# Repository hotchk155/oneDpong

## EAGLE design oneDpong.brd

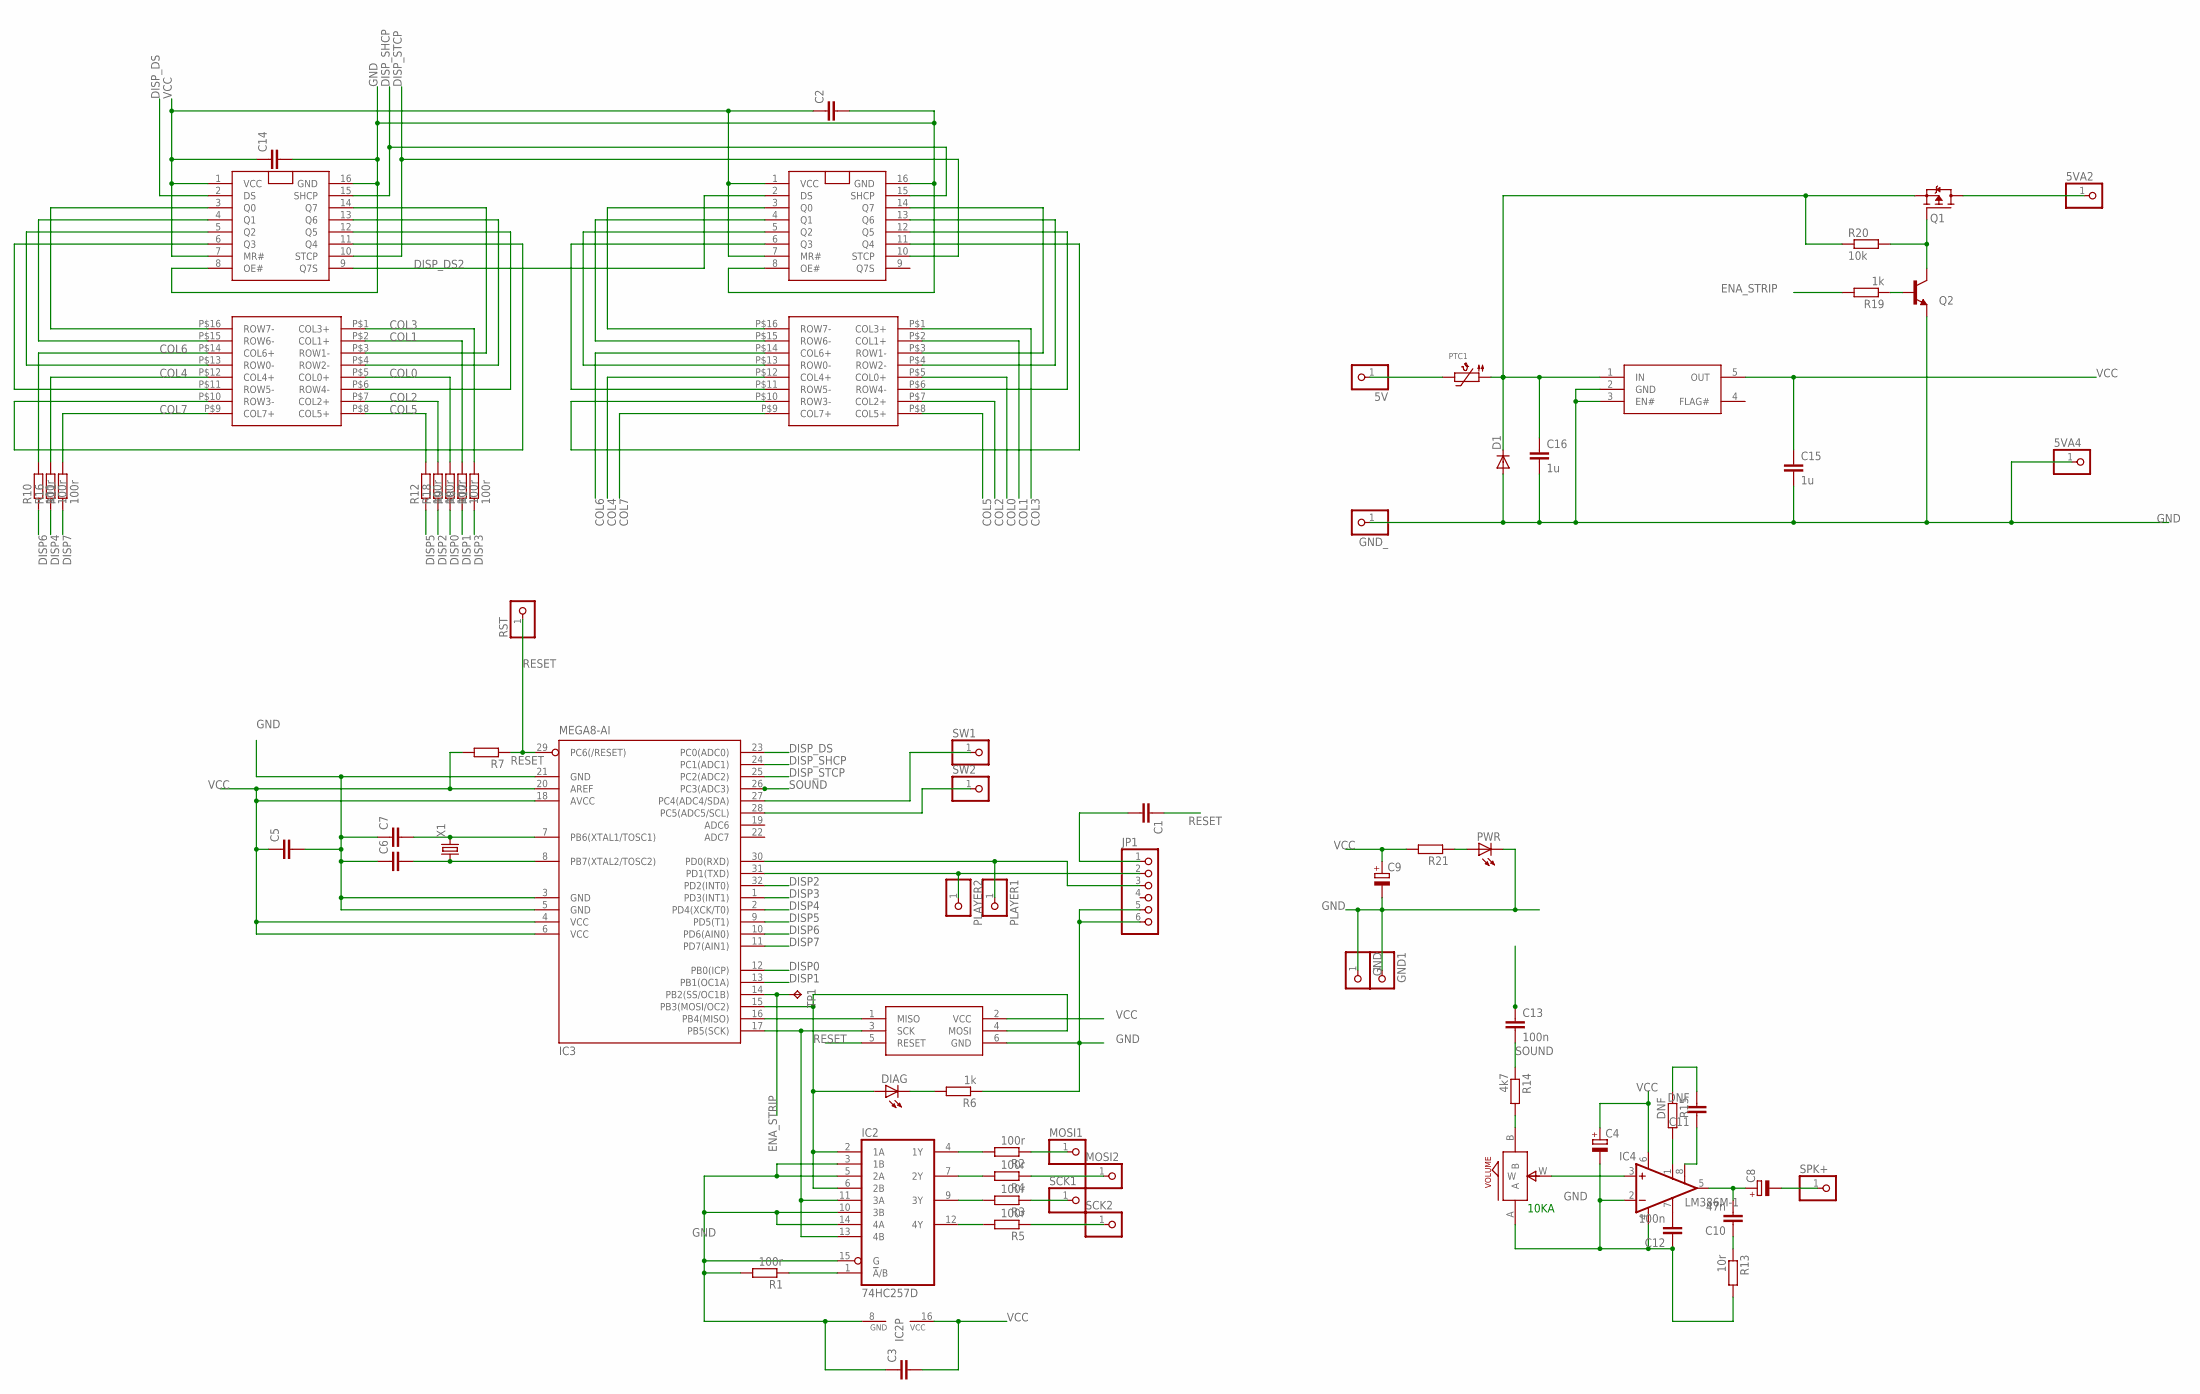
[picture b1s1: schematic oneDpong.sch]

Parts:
5V, 5VA2, 5VA4: PINHD-1X1; 1X01
C1, C2, C3, C5, C6, C7, C14: C-EUC0805; C0805
C4, C8, C9: CPOL-EUE2.5-6; E2,5-6
C10: 47n; C0805
C11: DNF; C0805
C12, C13: 100n; C0805
C15, C16: 1u; C0805
D1: DIODE-SMC; SMC
DIAG: LED3MM
GND, GND1: PINHD-1X1; 1X01
GND_: PINHD-1X1; 1X01
IC1, IC5: NPIC6C596; SO16
IC2: 74HC257D; SO16
IC3: MEGA8-AI; TQFP32-08
IC4: LM386M-1; SO08
IC6: NCP361SNT1G; SOT23-5
ICSP: TAG_CONN_AVR; TC2030-MCP-NL
JP1: PINHD-1X6; 1X06
MOSI1, MOSI2: PINHD-1X1; 1X01
PLAYER1, PLAYER2: PINHD-1X1; 1X01
PTC1: PTC1812
PWR: LED3MM
Q1: SPD30P06PTO252; TO252
Q2: MMBT3904LT1-NPN-SOT23-BEC; SOT23-BEC
R1, R2, R3, R4, R5, R8, R9, R10, R11, R12, R16, R17, R18: 100r; R0805
R6, R19: 1k; R0805
R7, R21: R-EU_R0805; R0805
R13: 10r; R0805
R14: 4k7; R0805
R15: DNF; R0805
R20: 10k; R0805
RST: PINHD-1X1; 1X01
SCK1, SCK2: PINHD-1X1; 1X01
SPK+: PINHD-1X1; 1X01
SW1, SW2: PINHD-1X1; 1X01
TP1: TPB1,27; B1,27
U$1, U$2: LARGE8X8
VOLUME: ALPS_POT_SMALL; SMALL_ALPS_POT
X1: CRYSTALHC49U-V; HC49U-V

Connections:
COL0: R9.2, U$1.P$5 (COL0+), U$2.P$5 (COL0+)
COL1: R8.2, U$1.P$2 (COL1+), U$2.P$2 (COL1+)
COL2: R18.2, U$1.P$7 (COL2+), U$2.P$7 (COL2+)
COL3: R17.2, U$1.P$1 (COL3+), U$2.P$1 (COL3+)
COL4: R16.2, U$1.P$12 (COL4+), U$2.P$12 (COL4+)
COL5: R12.2, U$1.P$8 (COL5+), U$2.P$8 (COL5+)
COL6: R10.2, U$1.P$14 (COL6+), U$2.P$14 (COL6+)
COL7: R11.2, U$1.P$9 (COL7+), U$2.P$9 (COL7+)
DISP0: IC3.12 (PB0(ICP)), R9.1
DISP1: IC3.13 (PB1(OC1A)), R8.1
DISP2: IC3.32 (PD2(INT0)), R18.1
DISP3: IC3.1 (PD3(INT1)), R17.1
DISP4: IC3.2 (PD4(XCK/T0)), R16.1
DISP5: IC3.9 (PD5(T1)), R12.1
DISP6: IC3.10 (PD6(AIN0)), R10.1
DISP7: IC3.11 (PD7(AIN1)), R11.1
DISP_DS: IC3.23 (PC0(ADC0)), IC5.2 (DS)
DISP_DS2: IC1.2 (DS), IC5.9 (Q7S)
DISP_SHCP: IC1.15 (SHCP), IC3.24 (PC1(ADC1)), IC5.15 (SHCP)
DISP_STCP: IC1.10 (STCP), IC3.25 (PC2(ADC2)), IC5.10 (STCP)
ENA_STRIP: IC3.14 (PB2(SS/OC1B)), R19.2, TP1.TP
GND: 5VA4.1, C2.2, C3.1, C4.-, C5.2, C6.1, C7.1, C9.-, C12.1, C14.2, C15.2, C16.2, D1.A, GND.1, GND1.1, GND_.1, IC1.8 (OE#), IC1.16 (GND), IC2.3 (1B), IC2.5 (2A), IC2.8 (GND), IC2.10 (3B), IC2.14 (4A), IC2.15 (G), IC3.3 (GND), IC3.5 (GND), IC3.21 (GND), IC4.2 (-IN), IC4.4 (GND), IC5.8 (OE#), IC5.16 (GND), IC6.2 (GND), IC6.3 (EN#), ICSP.6 (GND), JP1.5, JP1.6, PWR.K (C), Q2.E, R1.2, R6.1, R13.2, VOLUME.A
MISO: IC3.16 (PB4(MISO)), ICSP.1 (MISO)
MOSI2: MOSI2.1, R4.1
unnamed: IC3.30 (PD0(RXD)), JP1.3, PLAYER1.1
unnamed: IC2.1 (!A!/B), R1.1
unnamed: C7.2, IC3.7 (PB6(XTAL1/TOSC1)), X1.2
unnamed: C6.2, IC3.8 (PB7(XTAL2/TOSC2)), X1.1
unnamed: IC2.4 (1Y), R2.2
unnamed: IC2.7 (2Y), R4.2
unnamed: IC2.11 (3A), IC2.13 (4B), IC3.17 (PB5(SCK)), ICSP.3 (SCK)
unnamed: C10.1, R13.1
unnamed: C1.2, JP1.1
unnamed: IC2.9 (3Y), R3.2
unnamed: IC2.12 (4Y), R5.2
unnamed: MOSI1.1, R2.1
unnamed: 5VA2.1, Q1.3 (D)
unnamed: IC3.31 (PD1(TXD)), JP1.2, PLAYER2.1
unnamed: R5.1, SCK2.1
unnamed: R14.2, VOLUME.B
unnamed: IC4.3 (+IN), VOLUME.W
unnamed: IC3.28 (PC5(ADC5/SCL)), SW2.1
unnamed: C8.+, C10.2, IC4.5 (OUT)
unnamed: C8.-, SPK+.1
unnamed: C12.2, IC4.7 (BYPASS)
unnamed: IC4.1 (GAIN), R15.2
unnamed: C11.2, R15.1
unnamed: C11.1, IC4.8 (GAIN)
unnamed: C13.2, R14.1
unnamed: PWR.A, R21.1
unnamed: DIAG.K (C), R6.2
unnamed: 5V.1, PTC1.P$2 (2)
unnamed: Q1.1 (G), Q2.C, R20.2
unnamed: Q2.B, R19.1
PMOSI: DIAG.A, IC2.2 (1A), IC2.6 (2B), IC3.15 (PB3(MOSI/OC2)), ICSP.4 (MOSI)
Q0A: IC5.3 (Q0), U$1.P$16 (ROW7-)
Q0A1: IC1.3 (Q0), U$2.P$16 (ROW7-)
Q1A: IC5.4 (Q1), U$1.P$15 (ROW6-)
Q1A1: IC1.4 (Q1), U$2.P$15 (ROW6-)
Q2A: IC5.5 (Q2), U$1.P$13 (ROW0-)
Q2A1: IC1.5 (Q2), U$2.P$13 (ROW0-)
Q3A: IC5.6 (Q3), U$1.P$11 (ROW5-)
Q3A1: IC1.6 (Q3), U$2.P$11 (ROW5-)
Q4A: IC5.11 (Q4), U$1.P$10 (ROW3-)
Q4A1: IC1.11 (Q4), U$2.P$10 (ROW3-)
Q5A: IC5.12 (Q5), U$1.P$6 (ROW4-)
Q5A1: IC1.12 (Q5), U$2.P$6 (ROW4-)
Q6A: IC5.13 (Q6), U$1.P$4 (ROW2-)
Q6A1: IC1.13 (Q6), U$2.P$4 (ROW2-)
Q7A: IC5.14 (Q7), U$1.P$3 (ROW1-)
Q7A1: IC1.14 (Q7), U$2.P$3 (ROW1-)
RESET: C1.1, IC3.29 (PC6(/RESET)), ICSP.5 (RESET), R7.1, RST.1
SCK1: R3.1, SCK1.1
SOUND: C13.1, IC3.26 (PC3(ADC3))
SW1: IC3.27 (PC4(ADC4/SDA)), SW1.1
VCC: C2.1, C3.2, C4.+, C5.1, C9.+, C14.1, C15.1, IC1.1 (VCC), IC1.7 (MR#), IC2.16 (VCC), IC3.4 (VCC), IC3.6 (VCC), IC3.18 (AVCC), IC3.20 (AREF), IC4.6 (VS), IC5.1 (VCC), IC5.7 (MR#), IC6.5 (OUT), ICSP.2 (VCC), R7.2, R21.2
VIN: C16.1, D1.C, IC6.1 (IN), PTC1.P$1 (1), Q1.2 (S), R20.1

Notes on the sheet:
10KA

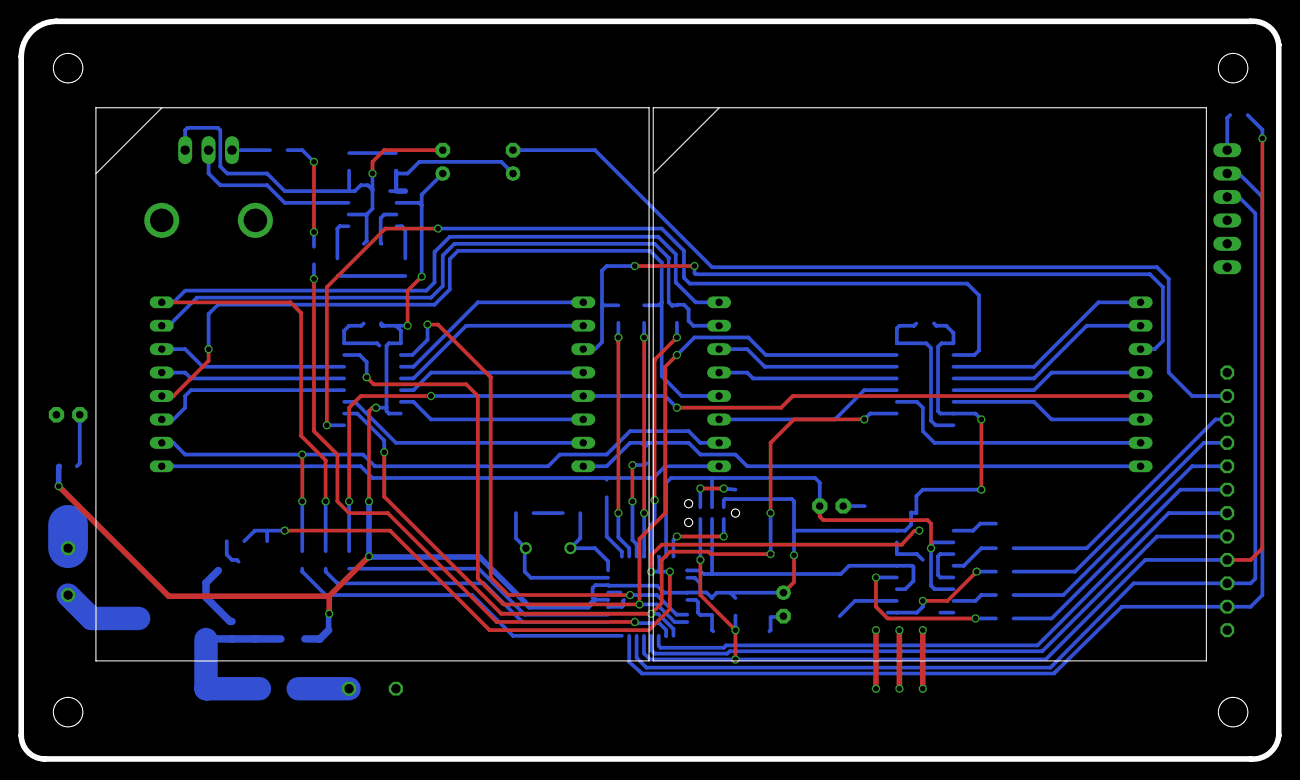
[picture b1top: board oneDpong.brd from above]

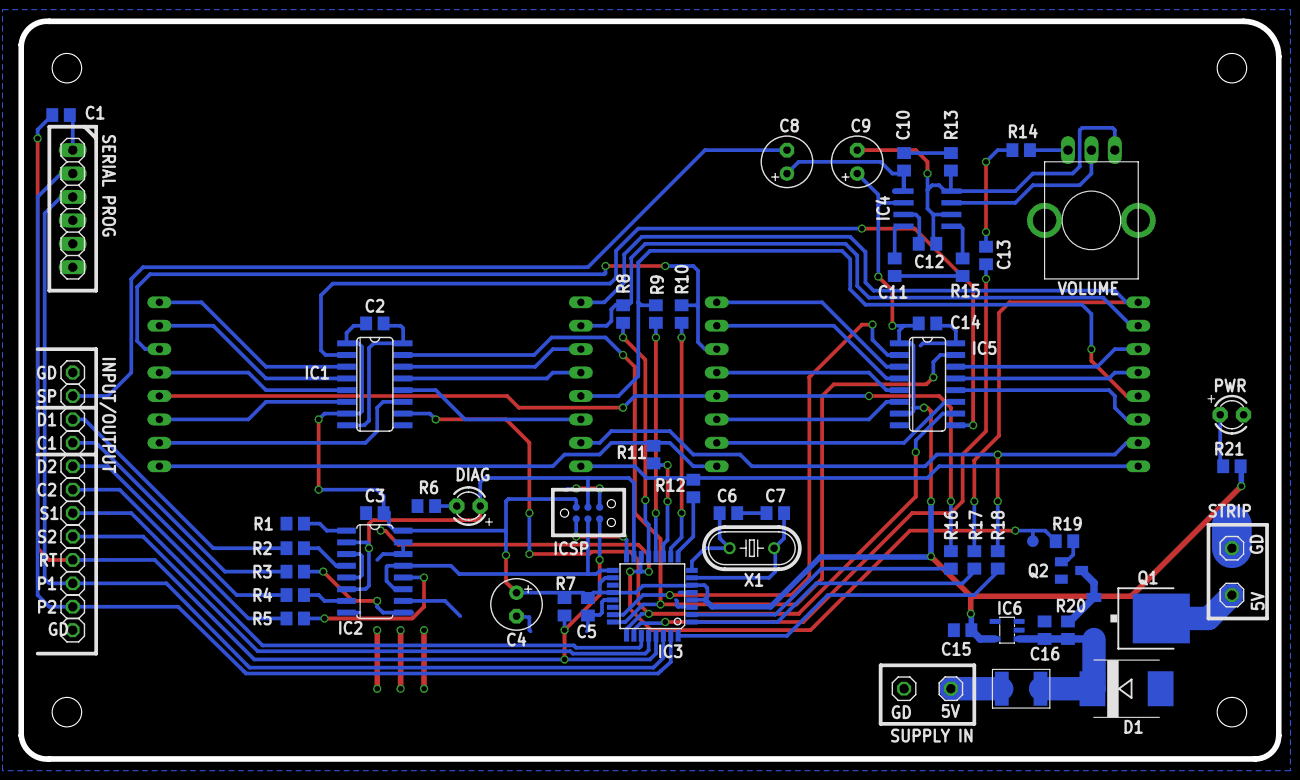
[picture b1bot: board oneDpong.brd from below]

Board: 2 copper layers, 136.4 x 80.0 mm, 72 parts (70 on the bottom side), 77 nets.

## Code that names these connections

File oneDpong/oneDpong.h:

#define P_DS    14 // PC0
#define P_SHCP  15 // PC1
#define P_STCP  16 // PC2
#define P_D0 8 // PB0
#define P_D1 9 // PB1
#define P_D2 2 // PD2
#define P_D3 3 // PD3
#define P_D4 4 //PD4
#define P_D5 5 //PD5
#define P_D6 6 // PD6
#define P_D7 7 // PD7
#define P_SOUND 17
#define P_PLAYER1 0
#define P_PLAYER2 1

#define P_SELECT 18
#define P_INPUT  19
#define P_ENABLE_STRIP 10

enum {
  EVENT_NONE,
  EVENT_P1_PRESS,
  EVENT_P2_PRESS,
  EVENT_P1_RELEASE,
  EVENT_P2_RELEASE
};

// enumeration of games
enum {
  GAME_PONG,
  GAME_PONG_1P,
  GAME_BREAKOUT,
  GAME_MAX
};

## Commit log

2015-05-10 :lollipop: Added .gitattributes & .gitignore files
2015-05-10 tweaks
2015-05-29 more tweaks
2015-05-29 pcb ready
2015-07-26 in progress
2015-08-12 stiuff
2015-08-17 charset
2015-08-21 stuff
2015-08-29 add overvoltage protect, refactor
2015-09-25 game over, title screen
2017-07-17 bits
2017-07-17 tidy up values
2019-10-09 poss V3
2019-10-09 V3 BOARD
2019-12-27 strip enable

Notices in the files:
oneDpong.brd:
creativecommons.org/licenses/by-nc-sa/4.0
parts and their libraries:
jasons_stuff: ©2009 ROFA.cz - modified and updated by Robert Darlington ‹rdarlington@gmail.com›
